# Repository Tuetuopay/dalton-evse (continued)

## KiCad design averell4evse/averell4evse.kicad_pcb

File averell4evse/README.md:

# averell4evse

The largest PCB housing the input devices (NFC, touch).

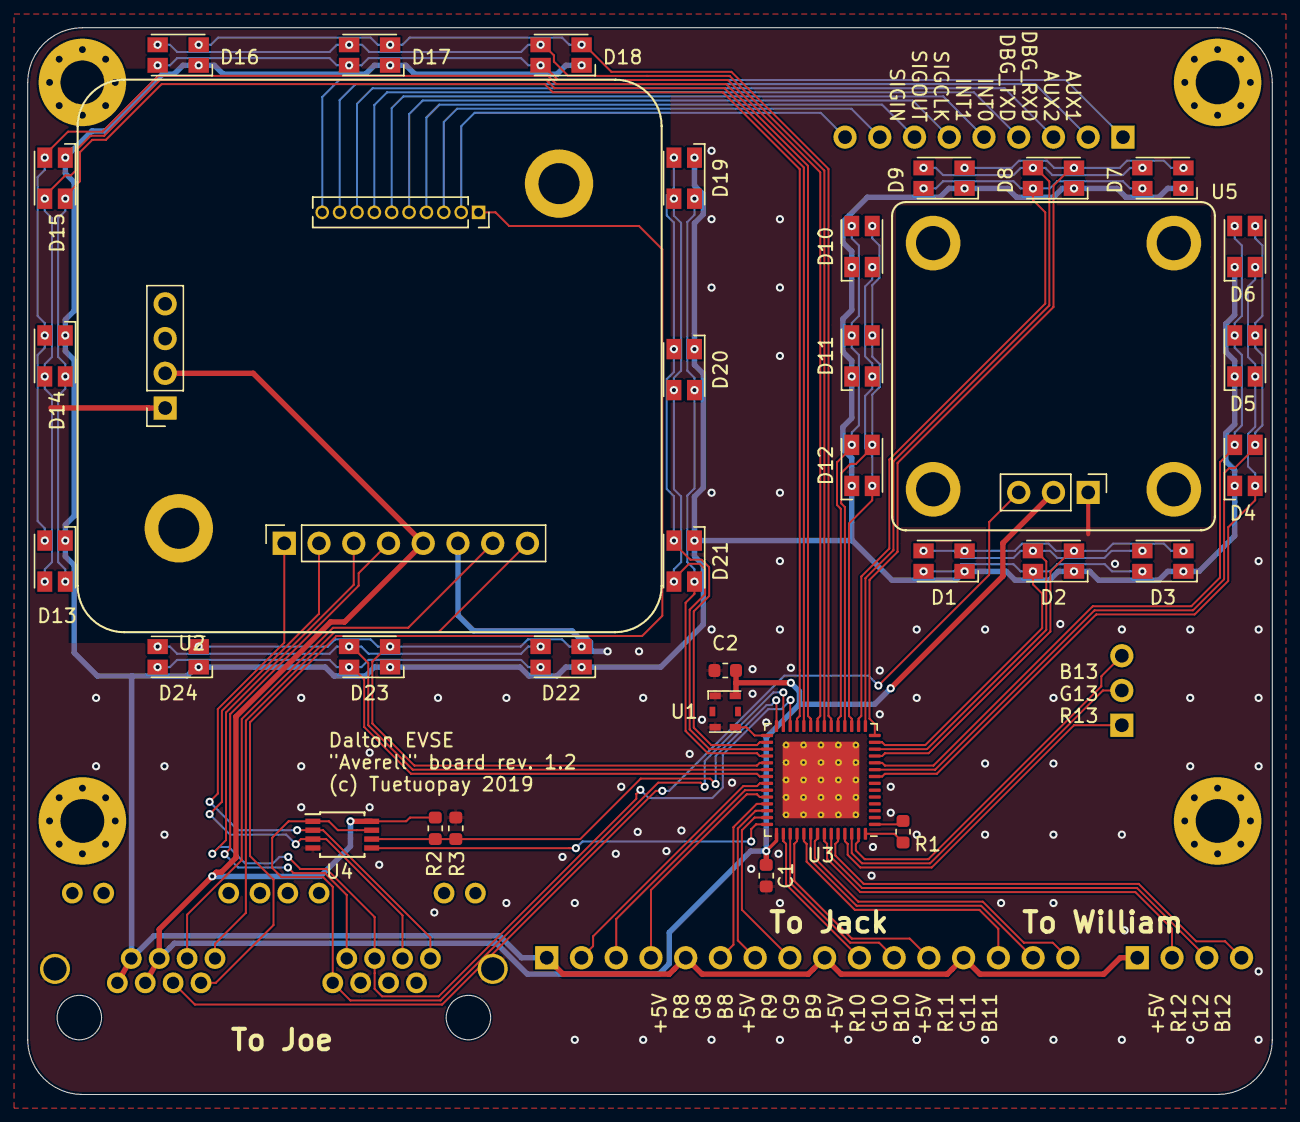
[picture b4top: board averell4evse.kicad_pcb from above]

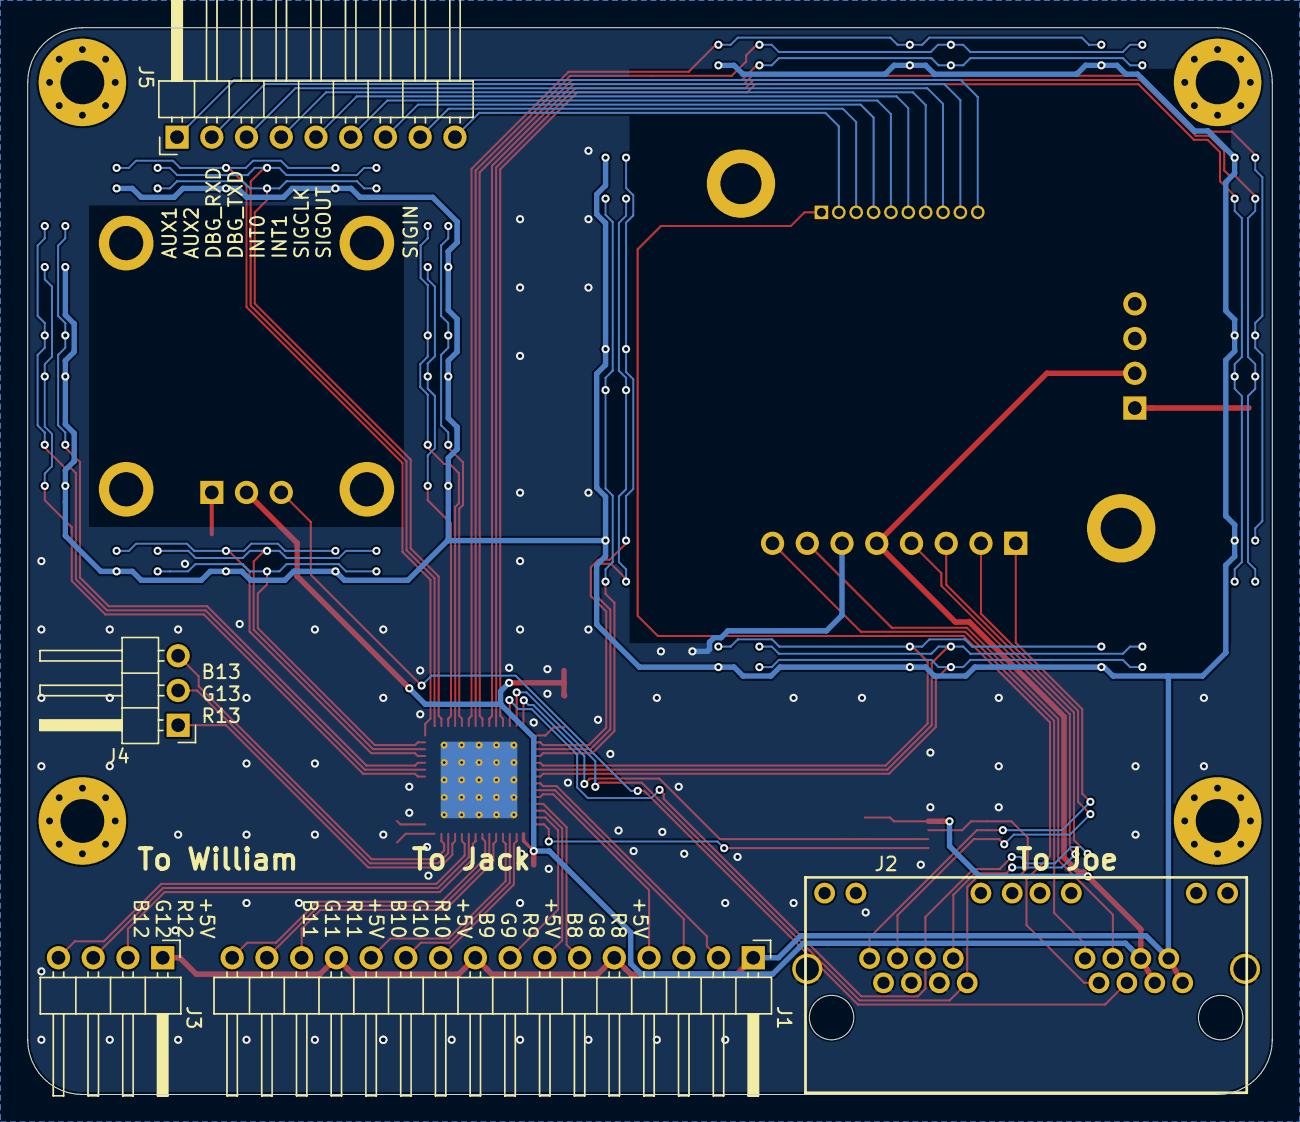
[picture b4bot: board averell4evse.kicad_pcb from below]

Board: 2 copper layers, 91.0 x 78.0 mm, 39 parts (5 on the bottom side), 68 nets.

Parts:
C1, C2: 1u; C_0603_1608Metric
D1, D2, D3, D4, D5, D6, D7, D8, D9, D10, D11, D12, D13, D14, D15, D16, D17, D18, D19, D20, D21, D22, D23, D24: ASMB-MTB0-0A3A2; LED_Avago_PLCC4_3.2x2.8mm_CW
J1: Conn_01x16; PinHeader_1x16_P2.54mm_Horizontal
J2: CONNFLY_Elec_DS1129-04-S8B0P-X
J3: Conn_01x04; PinHeader_1x04_P2.54mm_Horizontal
J4: Conn_01x03; PinHeader_1x03_P2.54mm_Horizontal
J5: Conn_01x09; PinHeader_1x09_P2.54mm_Horizontal
R1: 8k; R_0603_1608Metric
R2, R3: 10k; R_0603_1608Metric
U1: KT2520K-T; Oscillator_SMD_Kyocera_2520-6Pin_2.5x2.0mm
U2: NFCv4; nfc_v4_mirror
U3: TLC5957RTQ; QFN-56-1EP_8x8mm_P0.5mm_EP5.6x5.6mm_ThermalVias
U4: 74AUC2G125; TSSOP-8_3x3mm_P0.65mm
U5: touch_sensor

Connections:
+3V3: C1.1, C2.1, J2.B3, J2.B4, R2.1, U1.6, U2.5, U2.10, U3.43, U4.8, U5.2
+5V: D1.1, D2.1, D3.1, D4.1, D5.1, D6.1, D7.1, D8.1, D9.1, D10.1, D11.1, D12.1, D13.1, D14.1, D15.1, D16.1, D17.1, D18.1, D19.1, D20.1, D21.1, D22.1, D23.1, D24.1, J1.1, J1.5, J1.9, J1.13, J2.B1, J2.B2, J3.1
/AUX1: J5.1, U2.22
/AUX2: J5.2, U2.21
/B0: D4.2, D5.2, D6.2, U3.10
/B1: D1.2, D2.2, D3.2, U3.13
/B2: D7.2, D8.2, D9.2, U3.16
/B3: D10.2, D11.2, D12.2, U3.19
/B4: D16.2, D17.2, D18.2, U3.22
/B5: D13.2, D14.2, D15.2, U3.25
/B6: D19.2, D20.2, D21.2, U3.32
/B7: D22.2, D23.2, D24.2, U3.35
/B8: J1.4, U3.38
/B9: J1.8, U3.41
/B10: J1.12, U3.46
/B11: J1.16, U3.49
/B12: J3.4, U3.52
/DBG_RXD: J5.3, U2.20
/DBG_TXD: J5.4, U2.19
/DRV_CS: J2.A1, U3.27, U4.1, U4.7
/DRV_SCK: R2.2, R3.1, U3.28, U4.6
/G0: D4.3, D5.3, D6.3, U3.9
/G1: D1.3, D2.3, D3.3, U3.12
/G2: D7.3, D8.3, D9.3, U3.15
/G3: D10.3, D11.3, D12.3, U3.18
/G4: D16.3, D17.3, D18.3, U3.21
/G5: D13.3, D14.3, D15.3, U3.24
/G6: D19.3, D20.3, D21.3, U3.31
/G7: D22.3, D23.3, D24.3, U3.34
/G8: J1.3, U3.37
/G9: J1.7, U3.40
/G10: J1.11, U3.45
/G11: J1.15, U3.48
/G12: J3.3, U3.51
/GCLK: U1.4, U3.29
/INT0: J5.5, U2.18
/INT1: J5.6, U2.17
/IRQ: J2.B6, U2.7
/LED_MISO: U3.42, U4.5
/MISO: J2.A6, U2.2, U4.3
/MOSI: J2.A4, U2.3, U3.26
/NFC_CS: J2.A2, U2.4
/R0: D4.4, D5.4, D6.4, U3.8
/R1: D1.4, D2.4, D3.4, U3.11
/R2: D7.4, D8.4, D9.4, U3.14
/R3: D10.4, D11.4, D12.4, U3.17
/R4: D16.4, D17.4, D18.4, U3.20
/R5: D13.4, D14.4, D15.4, U3.23
/R6: D19.4, D20.4, D21.4, U3.30
/R7: D22.4, D23.4, D24.4, U3.33
/R8: J1.2, U3.36
/R9: J1.6, U3.39
/R10: J1.10, U3.44
/R11: J1.14, U3.47
/R12: J3.2, U3.50
/SCK: J2.A8, U2.1, U4.2
/SIGCLK: J5.7, U2.16
/SIGIN: J5.9, U2.14
/SIGOUT: J5.8, U2.15
/TOUCH: J2.B5, U5.3
/~RST: J2.B7, U2.13
/~RSTO: J2.B8, U2.8
GND: C1.2, C2.2, J2.A3, J2.A5, J2.A7, J2.SH, R3.2, U1.1, U1.3, U2.6, U2.9, U3.57, U4.4, U5.1
unnamed: J4.1, U3.53
unnamed: J4.2, U3.54
unnamed: J4.3, U3.55
unnamed: R1.1, U3.1
unnamed: R1.2, U3.56

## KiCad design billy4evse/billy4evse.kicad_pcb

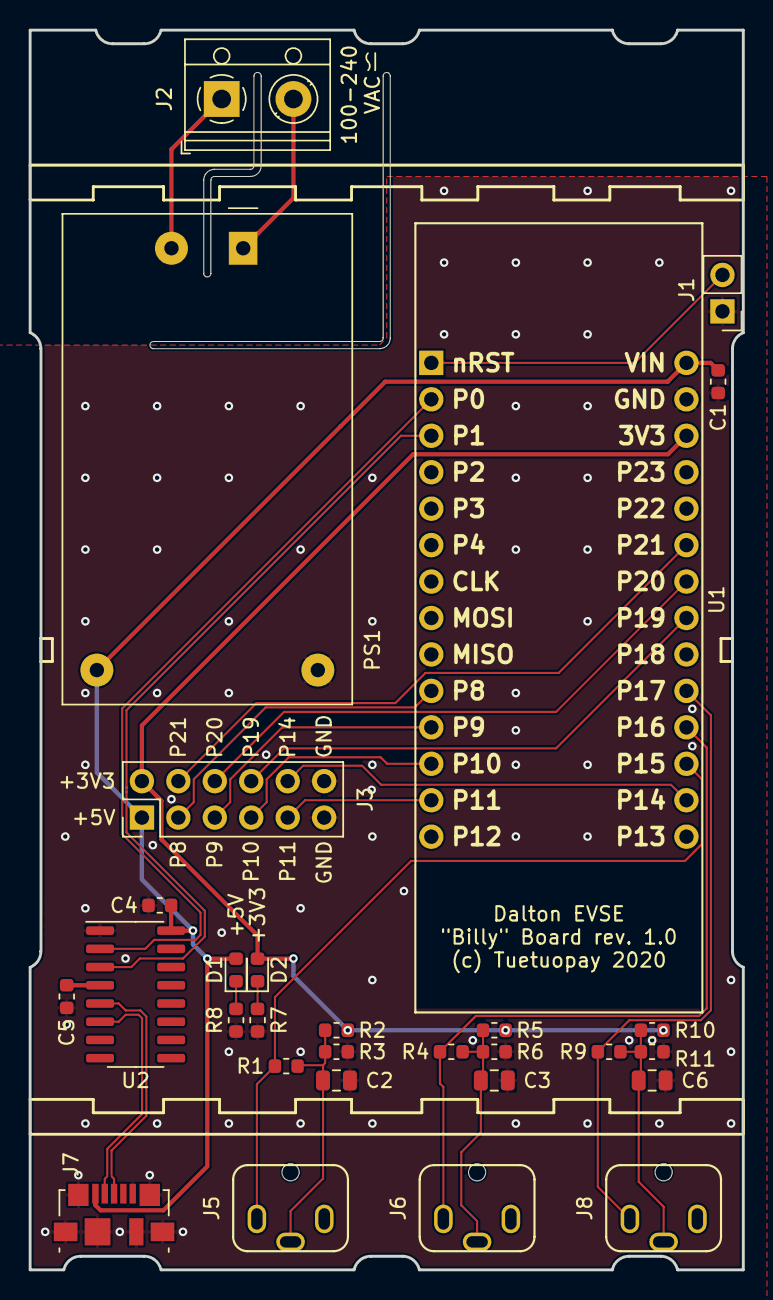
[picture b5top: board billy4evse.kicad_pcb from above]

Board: 2 copper layers, 49.7 x 86.4 mm, 29 parts (0 on the bottom side), 27 nets.

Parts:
C1, C4, C5: 100n; C_0603_1608Metric
C2, C3, C6: 10u; C_0805_2012Metric
D1: Red; LED_0603_1608Metric
D2: Orange; LED_0603_1608Metric
J1: Conn_01x02; PinHeader_1x02_P2.54mm_Vertical
J2: Screw_Terminal_01x02; TerminalBlock_RND_205-00012_1x02_P5.00mm_Horizontal
J3: Conn_02x06_Odd_Even; PinHeader_2x06_P2.54mm_Vertical
J5, J6, J8: AudioJack3; JIS-C-6560
J7: USB_B_Micro; USB_Micro-B_Molex_47346-0001
PS1: HLK-PM01; Converter_ACDC_HiLink_HLK-PMxx
R1, R4, R9: 23; R_0603_1608Metric
R2, R3, R5, R6, R10, R11: 10k; R_0603_1608Metric
R7: 3k; R_0603_1608Metric
R8: 1k; R_0603_1608Metric
U1: LoPy; fipy
U2: CH340C; SOIC-16_3.9x9.9mm_P1.27mm

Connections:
+3V3: D2.2, J3.2, R2.2, R5.2, R10.2, U1.26
+5V: C1.2, C4.2, D1.2, J3.1, J7.1, PS1.4, U1.28, U2.16
/AC_L: J2.2, PS1.1
/AC_N: J2.1, PS1.2
/CT0: J5.S, R1.2, U1.17
/CT1: J6.S, R4.2, U1.18
/CT2: J8.S, R9.2, U1.19
/LOPY2USB: U1.3, U2.3
/P8: J3.3, U1.10
/P9: J3.5, U1.11
/P10: J3.7, U1.12
/P11: J3.9, U1.13
/P14: J3.10, U1.16
/P19: J3.8, U1.21
/P20: J3.6, U1.22
/P21: J3.4, U1.23
/USB2LOPY: U1.2, U2.2
/USB_N: J7.2, U2.6
/USB_P: J7.3, U2.5
GND: C1.1, C2.1, C3.1, C4.1, C5.1, C6.1, J1.1, J3.11, J3.12, J7.5, J7.6, PS1.3, R3.1, R6.1, R7.2, R8.2, R11.1, U1.27, U2.1
unnamed: C2.2, J5.T, R1.1, R2.1, R3.2
unnamed: C3.2, J6.T, R4.1, R5.1, R6.2
unnamed: C5.2, U2.4
unnamed: C6.2, J8.T, R9.1, R10.1, R11.2
unnamed: D1.1, R7.1
unnamed: D2.1, R8.1
unnamed: J1.2, U1.1

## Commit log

2022-01-18 ma/sym: Import symbols from devkit
2022-01-18 ma/footprint: Add FiPy footprint
2022-01-18 ma: Initial commit with empty libraries
2022-01-18 ma/fp: Add male 2x8 1.27mm pin headers
2022-01-18 averell/pcb: Add conn + copyright to silkscreen
2022-01-18 ma/fp: Add 2x8 1.27mm female pin socket
2022-01-18 averell: Initial commit
2022-01-18 jack/sch: Switch main headers to 1x16
2022-01-18 ma/fp: Add NFC v4 footprint
2022-01-18 ma/fp: Add mirrored NFCv4 when mounted components facing down
2022-01-18 averell/*: Make a real CS for LED driver
2022-01-18 jack: Add square notch to board outline for main headers
2022-01-18 jack: Initial commit
2022-01-18 averell/pcb: Add DRV_CS to Joe connector silkscreen
2022-01-18 averell/sch: Change Joe connector to RJ45
2022-01-18 averell: Bump ma4evse version and fix its path
2022-01-18 averell/pcb: First draft, dimensions and placement done
2022-01-18 averell: Replace test pads with 0.1" pin headers
2022-01-18 averell/pcb: Add keepout zone under the NFC module
2022-01-18 averell/sch: Swap test pad footprints from pad to plated hole
2022-01-18 ma/fp: Add touch sensor module footprint
2022-01-18 averell/sch: Use mirrored NFCv4 footprint
2022-01-18 averell/pcb: Replace Joe connector with RJ45 jacks
2022-01-18 jack: Change LED footprint to ma ones
2022-01-18 averell/pcb: Fix some silkscreen labels placement
2022-01-18 averell/sch: Put 3 LEDs per channel rather than one
2022-01-18 jack/*: Add schematic and basic board layout
2022-01-18 ma/fp/nfc_v4: Add 3D model
2022-01-18 ma/fp: Add PLCC4 LED footprint with 3D model
2022-01-18 jack: Add ma submodule
2022-01-18 ma/pf: Rmove extra pad
2022-01-18 jack/pcb: Add enexten logo + rev info to silkscreen
2022-01-18 averell/sch: Annotate schematic
2022-01-18 averell/*: Update LED footprint with custom internal one
2022-01-18 joe: Initial commit
2022-01-18 jack/pcb: Done routing
2022-01-18 averell/pcb: Routing done
2022-01-18 averell/pcb: Add Enexten logo to silkscreen
2022-01-18 averell/sch: Assign PCB footprints
2022-01-18 averell/sch: First revision of the schematic done
2022-01-18 joe: Add enexten-devkit schematic in joe
2022-01-18 ma/fp: Nicer looking NFCv4 footprint
2022-01-18 averell/pcb: Add measurements to Dwgs.User layer
2022-01-18 averell/pcb: Fix LTC5957 exposed pad connection to ground plane
2022-01-18 averell/sch: Add power flags to make ERC happy
2022-01-18 jack: Re-route board with new connector and new board outline
2022-01-18 averell/pcb: Re-route with mirror NFCv4 module
2022-01-18 averell/sch: Swap LEDs text
2022-01-18 ma/sym: Add NFCv4 module symbol
2022-01-18 averell/pcb: Re-route LEDs with three per side
2022-01-18 ma/fp: Add Enexten logo
2022-01-18 joe: Add FIPY Pinout
2022-01-18 ma: Add single and dual RJ45 connectors
2022-01-18 averell/pcb: Add ground plane keepout under the touch sensor
2022-01-18 joe: Fix library path
2022-01-18 ma/fp: Add audio jack footprint
2022-01-18 joe/*: Rename LED_CS signal to LED_LAT
2022-01-18 joe/*: Add 0.1" header for easy access to RJ45 signals
2022-01-18 ma/3d: Add 3.5mm screw terminal model
2022-01-18 billy: Fix some DRC issues
2022-01-18 william/pcb: Add dimensions to Dwgs.User layer
2022-01-18 william: Rev. 1.1
2022-01-18 billy: Initial commit
2022-01-18 joe/sch: Assign footprints to components
2022-01-18 joe/pcb: Fix D13 footprint
2022-01-18 joe: Add 12V ERROUT
2022-01-18 billy: Add ma library
2022-01-18 billy{sch, pcb}: Finish LCSC P/N list and fix bottom-left PCB notch
2022-01-18 ma/3d: Add FiPY/LoPy 3D model
2022-01-18 william/pcb: Update with fixed RCMB footprint
2022-01-18 billy: Add clamping diodes to sensor inputs
2022-01-18 william: Add err_out relay output
2022-01-18 william: First version
2022-01-18 billy: Switch USB connector for vertical connector
2022-01-18 joe/pcb: Misc silk fixes
2022-01-18 billy{sch, pcb}: Add GPIO headers
2022-01-18 WIP: joe: Add errout signal
2022-01-18 joe/pcb: Routing done
2022-01-18 averell{sch, pcb}: Change oscillator and fix improper traces
2022-01-18 ma/{fp, 3d}: Add BC-53 DIN case
2022-01-18 ma/sym: Set RCMB121 footprint
2022-01-18 joe/sch: Schematic should be done
2022-01-18 billy{sch, pcb}: DIN-compatible second draft
2022-01-18 averell/*: Remove LED driver CS thingy
2022-01-18 ma/sym: Add DPDT switch and 1N4001 SMD equivalent
2022-01-18 william: Add CI
2022-01-18 ma/{fp, 3d}: Add vertical audio jack
2022-01-18 ma/3d: Add 2520 crystal oscillator
2022-01-18 joe/sch: Remove relays and only keep control circuitry
2022-01-18 billy{sch, pcb}: Add screw terminals on top for current sensors
2022-01-18 ma/3d: Add HLK-PM0x
2022-01-18 william: Initial commit
2022-01-18 averell/pcb: Move RJ45 connector and mounting screws backwards
2022-01-18 ma/3d: Add Würth 614105150721 Vertical USB µB
2022-01-18 ma/3d: Remove sample PCB from BC-53 cover model
2022-01-18 ma/fp: Fix RCMB121 pin positions
2022-01-18 joe/*: Connect charge pump boost pin to +12V
    This increases the switching frequency from 10kHz to 45kHz, making the
    pump capacitor resonating inaudible.
2022-01-18 joe/pcb: Rev 1.1
2022-01-18 ma/lib: Add AP3015 symbol
2022-01-18 joe/pcb: Placement should be done
2022-01-18 joe/sch: Remove relays and reference AC test to neutral rather than GND
2022-01-18 billy/pcb: Set HLK-PM01 3D model
2022-01-18 averell/pcb: Add silk with RJ45 numbering
2022-01-18 averell/pcb: Set xtal 3D model
2022-01-18 joe: Add temperature sensor
2022-01-18 ma/sym: Add LoPy symbol
2022-01-18 ma/3d: Add 2 position 5mm screw terminal
2022-01-18 ma/{fp, 3d}: Add audio jack 3D model
2022-01-18 billy/*: First billy draft
2022-01-18 jack/{sch, pcb}: Make one single ring pcb with all leds
2022-01-18 joe/{sch, pcb}: Swap some MCU pins for easier pinout
    - Swap P23/P13
    - Swap P21/P16
2022-01-18 billy/sch: List all LCSC P/N
2022-01-18 joe/lib: Misc KiCAD stuff
2022-01-18 joe/{sch, pcb}: Add missing temp sensor
2022-01-18 ma/*: Add symbols and footprints for Joe
2022-01-18 ma/{sym, fp}: Add RCMB121 module
2022-01-18 joe/sch: Add mounting holes
2022-01-18 william/pcb: Fix missing 5V trace
2022-01-18 joe/pcb: Rev 1.2
2022-01-18 joe/{sch, pcb}: Add 0r resistors in parallel of SW1 for prod boards
2022-01-18 ma/fp: Fix RCMB hole size
2022-01-18 william: Release v1.2
2022-01-18 william: Misc updates
    - Add power inductor in the power line
    - Swap TEST_IN and X30_OUT signals
    - Fix board outline to take RCMB bumps into account
    - Fix RCMB hole size
2022-01-18 william: Revert "Add err_out relay output"
    This reverts commit fe4c97044222ea82c6b882aa488b85d2dc32cb0e.
2022-01-18 ma/*: Fix line endings and file permissions
    Screw you, windows...
2022-01-18 william{sch, pcb}: Swap (again) wires
2022-01-18 joe/{sch, pcb}: Remove input shottky diodes
2022-01-18 william: Release v1.3
2022-01-18 joe/pcb: Rev v1.3
2022-01-18 joe/{sch, pcb}: Combine AC_RELAY and RCMB output
